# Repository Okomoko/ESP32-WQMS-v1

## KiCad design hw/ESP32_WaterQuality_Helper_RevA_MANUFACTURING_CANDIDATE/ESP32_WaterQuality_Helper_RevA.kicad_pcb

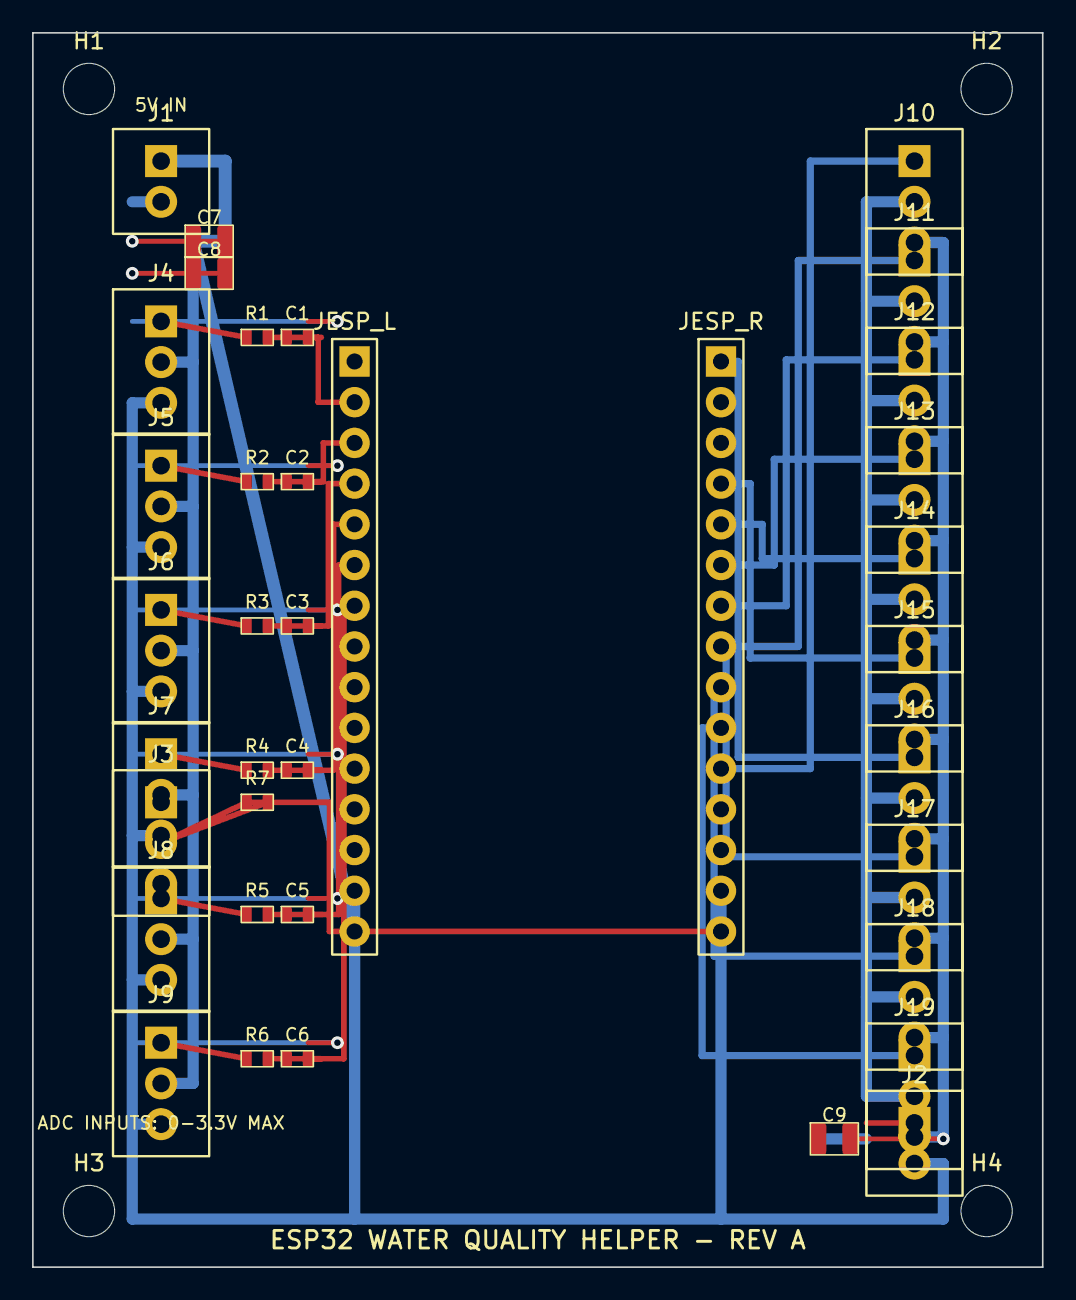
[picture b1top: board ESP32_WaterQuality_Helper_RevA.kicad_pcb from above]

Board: 2 copper layers, 63.0 x 77.0 mm, 41 parts (0 on the bottom side), 22 nets.

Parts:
C1, C2, C3, C4, C5, C6: 100nF; SMD
C7: 100uF; SMD
C8, C9: 47uF; SMD
H1, H2, H3, H4: M3
J1: +5V,GND; Custom_2P
J2: VREF_CAL,GND; Custom_2P
J3: +3V3,DATA,GND; Custom_3P
J4, J5, J6, J7, J8, J9: SIG,+5V,GND; Custom_3P
J10, J11, J12, J13, J14, J15, J16, J17, J18, J19: IN,+5V,GND; Custom_3P
JESP_L: ESP32 15P; ESP32_1x15
JESP_R: ESP32 15P; ESP32_1x15
R1, R2, R3, R4, R5, R6: 1k; SMD
R7: 10k; SMD

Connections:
+3V3: J3.1, JESP_R.15, R7.1
+5V_IN: C7.1, J1.1, JESP_L.15
+5V_RELAY: C9.1, J10.2, J11.2, J12.2, J13.2, J14.2, J15.2, J16.2, J17.2, J18.2, J19.2
+5V_SENSOR: C8.1, J4.2, J5.2, J6.2, J7.2, J8.2, J9.2
ADC_GPIO32: C5.1, J8.1, JESP_L.6, R5.1
ADC_GPIO33: C6.1, J9.1, JESP_L.7, R6.1
ADC_GPIO34: C3.1, J6.1, JESP_L.4, R3.1
ADC_GPIO35: C4.1, J7.1, JESP_L.5, R4.1
ADC_GPIO36: C1.1, J4.1, JESP_L.2, R1.1
ADC_GPIO39: C2.1, J5.1, JESP_L.3, R2.1
GND: J1.2, J2.2, J3.3, J4.3, J5.3, J6.3, J7.3, J8.3, J9.3, J10.3, J11.3, J12.3, J13.3, J14.3, J15.3, J16.3, J17.3, J18.3, J19.3, JESP_L.14, JESP_R.14
GPIO4: J10.1, JESP_R.11
GPIO5: J11.1, JESP_R.8
GPIO13: J3.2, JESP_L.13
GPIO18: J12.1, JESP_R.7
GPIO19: J13.1, JESP_R.6
GPIO21: J14.1, JESP_R.5
GPIO22: J15.1, JESP_R.2
GPIO23: J16.1, JESP_R.1
GPIO25: J17.1, JESP_L.8
GPIO26: J18.1, JESP_L.9
GPIO27: J19.1, JESP_L.10

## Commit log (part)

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2026-06-30 automation module updates
2026-06-30 Add filelist.txt with project file links
